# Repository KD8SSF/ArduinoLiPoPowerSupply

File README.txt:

MC34063 Step-up circuit: "Arduino Li-Po Power Supply"

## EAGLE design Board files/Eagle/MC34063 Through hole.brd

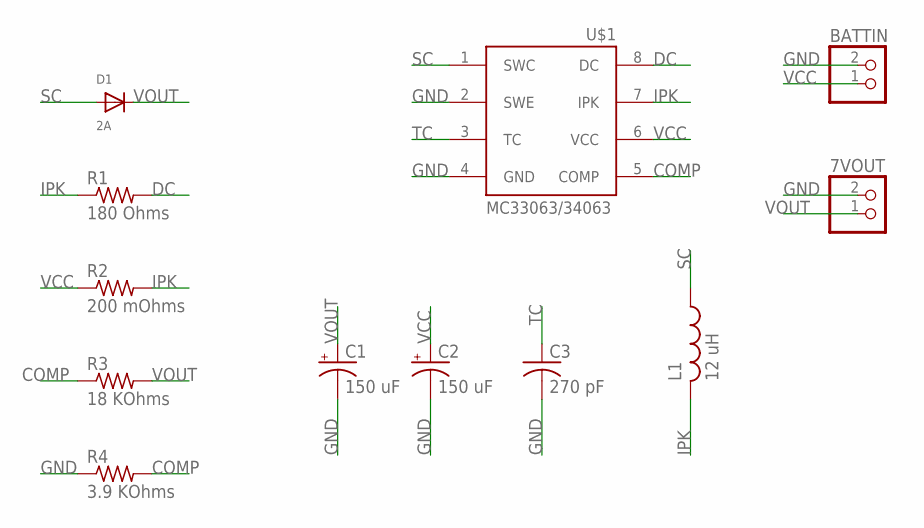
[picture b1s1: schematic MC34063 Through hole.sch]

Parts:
7VOUT: JST_2PIN-THM-RA; JST-PH-2-THM-RA
BATTIN: JST_2PIN-THM-RA; JST-PH-2-THM-RA
C1, C2: 150 uF; E2-5
C3: 270 pF; C050-024X044
D1: 2A; DO-1N4148
L1: 12 uH; 0207/5V
R1: 180 Ohms; 0207/2V
R2: 200 mOhms; 0207/2V
R3: 18 KOhms; 0207/2V
R4: 3.9 KOhms; 0207/2V
U$1: MC33063/MC34063P; DIL08

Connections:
COMP: R3.1, R4.2, U$1.5 (COMP)
DC: R1.2, U$1.8 (DC)
GND: 7VOUT.2 (1), BATTIN.2 (1), C1.-, C2.-, C3.2, R4.1, U$1.2 (SWE), U$1.4 (GND)
IPK: L1.2, R1.1, R2.2, U$1.7 (IPK)
SC: D1.A, L1.1, U$1.1 (SWC)
TC: C3.1, U$1.3 (TC)
VCC: BATTIN.1 (2), C2.+, R2.1, U$1.6 (VCC)
VOUT: 7VOUT.1 (2), C1.+, D1.C, R3.2

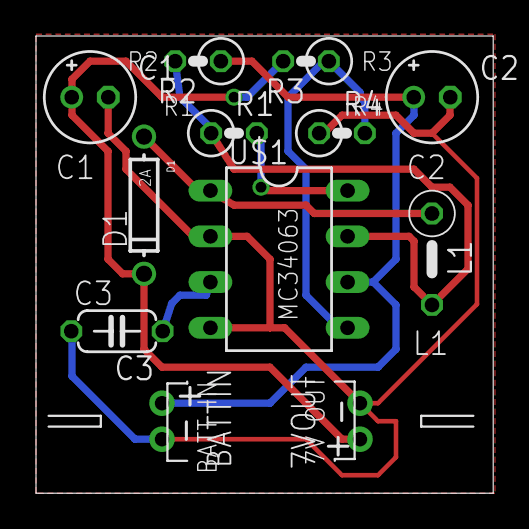
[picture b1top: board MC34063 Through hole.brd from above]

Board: 2 copper layers, 25.4 x 25.4 mm, 12 parts (0 on the bottom side), 8 nets.

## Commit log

2014-02-17 Publish
2014-02-17 Board files, datasheet
2014-02-17 Eagle files

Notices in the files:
Board files/Eagle/MC34063 Through hole.brd:
CC BY-NC-SA
